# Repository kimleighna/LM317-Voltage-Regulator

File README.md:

# LM317 Voltage Regulator — PCB Design Project

## Overview
Fabrication ready 2-layer PCB. Adjustable voltage regulator built 
around the LM317 TO-220. Designed end-to-end in KiCad: schematic 
capture, component selection, layout, routing, and full fabrication 
outputs including Gerbers and BOM.

## Components
| Reference | Component | Value | Package |
|-----------|-----------|-------|---------|
| U1 | LM317 Voltage Regulator | — | TO-220 |
| C1 | Electrolytic Capacitor | 1000µF | Radial THT |
| C2 | Electrolytic Capacitor | 200µF | Radial THT |
| R1 | Resistor | 250Ω | Axial THT |
| R2 | Resistor | 2.5kΩ | Axial THT |
| R3 | Resistor | 100Ω | Axial THT |
| J1 | 2-Pin Connector (Output) | — | PinHeader 2.54mm |
| J2 | 2-Pin Connector (Input) | — | PinHeader 2.54mm |

## Repo Structure
```
lm317-voltage-regulator/
├── kicad/          # Schematic and PCB layout files
├── gerbers/        # Gerber and drill files
├── bom/            # Bill of Materials (CSV)
└── docs/           # Schematic PDF and PCB layout PDFs
```

## Tools
- **KiCad** — Schematic, layout, DRC, Gerber export

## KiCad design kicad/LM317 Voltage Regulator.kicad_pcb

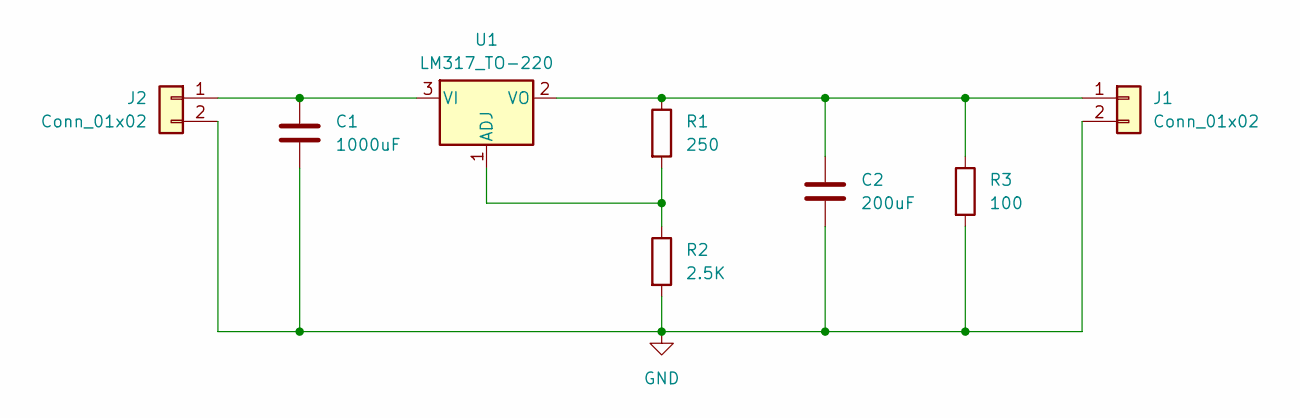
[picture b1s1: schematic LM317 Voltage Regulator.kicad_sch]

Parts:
C1: 1000uF; CP_Radial_D8.0mm_P3.50mm
C2: 200uF; CP_Radial_D8.0mm_P3.50mm
J1, J2: Conn_01x02; PinHeader_1x02_P2.54mm_Vertical
R1: 250; R_Axial_DIN0207_L6.3mm_D2.5mm_P10.16mm_Horizontal
R2: 2.5K; R_Axial_DIN0207_L6.3mm_D2.5mm_P10.16mm_Horizontal
R3: 100; R_Axial_DIN0207_L6.3mm_D2.5mm_P10.16mm_Horizontal
U1: LM317_TO-220; TO-220-3_Vertical

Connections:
GND: C1.2, C2.2, J1.2, J2.2, R2.2, R3.2
unnamed: C2.1, J1.1, R1.1, R3.1, U1.2 (VO)
unnamed: C1.1, J2.1, U1.3 (VI)
unnamed: R1.2, R2.1, U1.1 (ADJ)

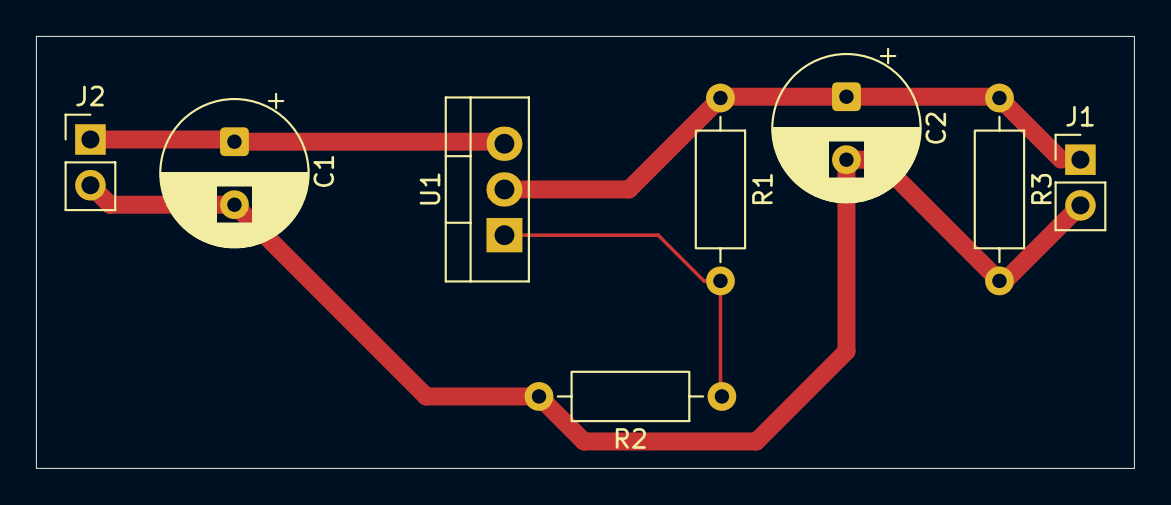
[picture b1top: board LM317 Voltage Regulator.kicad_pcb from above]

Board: 2 copper layers, 61.0 x 24.0 mm, 8 parts (0 on the bottom side), 4 nets.

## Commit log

2026-05-29 Create gerbers
